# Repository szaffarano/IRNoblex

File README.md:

## Implementación IR para controlar A/C Noblex modelo NOS32C13X

Es una versión preliminar, muy primitiva, deducida por ingeniería inversa analizando en osciloscopio y con un receiver TSOP48 en un Arduino.  En un raspberry pi si bien se pueden capturar tramas, los tiempos son muy dispares dada la latencia del sistema operativo.  No obtuve buenos resultados.

## Protocolo

### Nomenclatura

- Cada bit que se envía está conformado por un primer pulso (mark) que es igual siempre, más un segundo pulso (space) que varía según se quiera enviar un uno o un cero.
- Los valores de los pulsos son:
    + mark: 540 usec
    + space (cero): 520 usec
    + space (uno): 1580 usec
- Cada secuencia de bytes que se envía está conformada por:
    + un header, compuesto por un pulso mark de 8660 usec y un pulso space de 4300 usec.
    + 64 bits de información, con sucesivos marks y spaces según lo dicho antes.
    + Un bit "separador" que consiste un pulso mark de 640 y un pulso space de 19240.  Este separador se ubica en la posición 36 de la trama de 64 bits.
    + Cuatro bits que hacen las veces de checksum, calculado como la suma big endian de los 8 bytes precedentes interpretados también como big endian.

```
        +---+--------------+---+------------+-----+
        | H |   35 bits    |sep|   28 bits  | crc |
        +---+--------------+---+------------+-----+ 
```

### Modo

El código se codifica con 3 bits en la posición [0:3] de la trama.  El A/C maneja 5 modos distintos:

- Auto: 000
- Cool: 100
- Dry: 010
- Fan: 110
- Heat: 001

### Power

Es el 4 bit de la trama:

- On: 1
- Off: 0

### Fan

Se maneja con 2 bits en la posición [4:5] de la trama:

- Mínimo: 10
- Medio: 01
- Máximo: 11
- Auto: 00

### Swing

Se maneja con 2 bits.  Pueden ser más, falta analizar los distintos casos ya que por lo visto depende el modo en el que esté para que haya valores válidos.  En principió observé que se maneja con 2 bits **separados**, frame[5] y frame[36]

- On: ambos en uno.
- Off: ambos en cero.

### Temperatura

Manejada por 4 bits en la posición [8:11] del frame.  Se calcula como: TEMPERATURA - 16 y se expresa como big endian.

### Luz

Se representa con un bit en frame[21]. 

- On: 1
- Off: 0

### Bits invariantes / sin analizar

Solo una parte de los bits varían según la funcionalidad interpretada, el resto se mantiene invariante:

```c
  uint8_t frame[8] = {
    0,    // mode[0:2], power[3], fan[4:5], swing[6], zero[7]
    0,    // temp[0:3], zero[4:7]
    0,    // ligth[5], zero[0:4], one[6], zero[7]
    0x0A, // fixed[0:7]
    0x50, // fixed[0:3], separator[3], swing[4]
    0x00, // fixed[0:7]
    0x40, // fixed[0:7]
    0x00  // fixed[0:7]
  };
```

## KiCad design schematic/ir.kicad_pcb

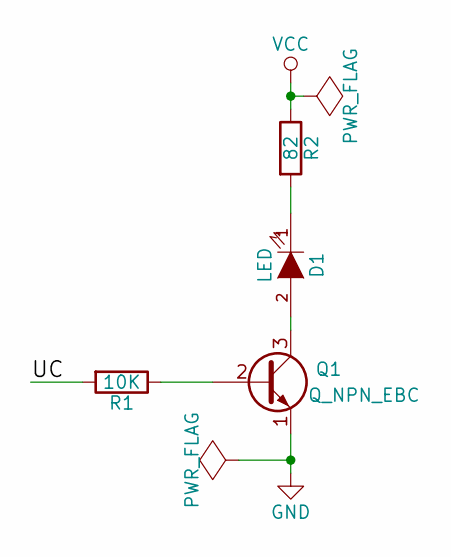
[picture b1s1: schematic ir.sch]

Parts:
D1: LED; LED-5MM
Q1: Q_NPN_EBC; TO-92_Inline_Wide
R1: 10K; Resistor_Horizontal_RM10mm
R2: 82; Resistor_Horizontal_RM10mm

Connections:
/UC: R1.2
GND: Q1.1 (E)
unnamed: D1.1 (K), R2.2
unnamed: D1.2 (A), Q1.3 (C)
unnamed: Q1.2 (B), R1.1
VCC: R2.1

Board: 2 copper layers, 4 parts (0 on the bottom side), 3 nets, no tracks yet.

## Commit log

2015-12-23 commit inicial
2015-12-23 Mejorar redacción
    amplío descripción del proyecto y documentación de comandos.
2015-12-23 Cambiar formato del readme
2015-12-24 Refactoring de algoritmo
    - se refactoriza el agoritmo solucionando problema de crc
    - se migra a platform.io para mejorar el proceso de build
    - se agrega configuración de proyecto sublimetext
    Funciona todo normalmente con un shell de pruebas.
2015-12-24 Estilo del readme
2015-12-29 First full working version
    Adapt the layout of the source code to Arduino's libraries layout.
    Make any changes in the API.
2015-12-29 Add travis CI config
2015-12-29 add libraries install in travis.yml for ci
2015-12-29 fix platformio json manifest format
2015-12-29 Add dependent IRremote lib; fixes
2015-12-29 Fix include path to internal archive directory
